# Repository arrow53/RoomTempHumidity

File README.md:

# RoomTempHumidity

A local whole-house temperature and humidity monitor. USB-powered room sensors
send measurements over Thread to a Raspberry Pi base unit, which stores history
and presents a touchscreen dashboard without requiring a cloud service.

## Actual Pi dashboard

Direct capture of the running Pi display on **2026-10-11**. This is the live-mode
application with one reporting prototype sensor, not simulated data. Readings and
freshness reflect the capture time.

## Design summary

```mermaid
flowchart LR
  S["USB room node<br/>SHT40 + nRF54L15"] -->|"Thread IPv6 / CoAP JSON"| R["nRF52840 DK<br/>RCP"]
  R -->|"Spinel / USB serial<br/>115200 RTS/CTS"| O["Pi 5<br/>OpenThread Border Router"]
  O --> C["Python collector<br/>aiocoap + SQLite"]
  C -->|"Loopback HTTP"| D["Browser kiosk<br/>Touch Display 2"]
```

- **Sensors:** SHT40 measures temperature and relative humidity. nRF54L15 firmware
  uses Zephyr and OpenThread, samples every minute and sends confirmable CoAP POSTs.
  Random boot IDs and sequence numbers support duplicate/replay handling. Continuous
  USB power permits an always-listening Thread router role.
- **Base radio:** pinned OpenThread RCP firmware on an nRF52840 DK connects over
  Spinel/UART through USB serial. It is separate from the sensor-node application.
- **Networking:** OTBR runs on the Pi 5. Recorded deployment limits forwarding to
  the intended local IPv6 LAN; IPv4 forwarding, NAT64, WebGUI and REST are disabled.
- **Collector/UI:** Python validates readings and stores bounded SQLite history.
  HTML/CSS/JavaScript provides room status, history and Celsius/Fahrenheit controls.
  CoAP bind retries keep the local dashboard available while a Thread address is
  missing. The Touch Display 2 presents the landscape browser/kiosk UI.
- **Protocol:** Thread + IPv6 + CoAP.

## Sensor hardware

| Enclosure A2 | Populated PCB A3 — angled 3D view |
| --- | --- |
|  |  |

The enclosure is a native OpenSCAD render. The populated PCB is a native KiCad
3D render of the unchanged A3 layout and its 16 component placements. Package
models show nominal geometry; the radio module uses a simplified dimension-based
body/shield. Neither image proves assembled hardware qualification.

The working prototype uses an **nRF54L15 DK and SHT40 breakout**. The custom
45 × 55 mm PCB uses Raytac AN54LQ-P15 and SHT40; A3 changes the regulator to
LT1761IS5-3.3#TRMPBF. Custom-board bring-up, printed fit, RF performance and thermal
bias remain unqualified. A3 is **quote/DFM only**, not production/purchase approval.

## Repository layout

| Directory | Contents |
| --- | --- |
| [SensorFirmware](SensorFirmware/README.md) | nRF54L15 DK firmware, pinned SDK manifest, schema and tests |
| [SensorCase](SensorCase/README.md) | A2 OpenSCAD, provisional print parts and fit coupons |
| [SensorPCB](SensorPCB/README.md) | Current A3 native KiCad and selected quote/DFM files |
| [BaseUnitFirmware](BaseUnitFirmware/README.md) | Pinned nRF52840 RCP source/build/UART reference |
| [BaseUnitApplication](BaseUnitApplication/README.md) | Pi collector/dashboard and sanitized OTBR reference |
| [BaseUnitCase](BaseUnitCase/README.md) | Revision C digital prototype, CAD and [print files](BaseUnitCase/revision-C/); physical validation pending |

Canonical workspace: `C:\GIT\RoomTempHumidity`. Future tasks should read
[AGENTS.md](AGENTS.md) and [migration notes](docs/MIGRATION.md).

## Technologies and methodology

Sensor firmware uses C, Nordic nRF Connect SDK **v3.2.1**, Zephyr and OpenThread.
RCP and OTBR use separate immutable upstream commits. OTBR's documented historical
build uses Debug after optimized builds failed a compiler diagnostic; warning and
runtime compatibility checks were retained.

The Pi application uses Python 3.11+, aiocoap, SQLite and HTML/CSS/JavaScript.
Mechanical design uses parametric OpenSCAD (sensor) and CadQuery (base case), static dimension checks and independent
STL topology checks. PCB work uses native KiCad schematic/layout, project-local
libraries, ERC/DRC and independent manufacturing-file audits.

Source, protocol fixtures and validation limits are preserved separately from local
deployment configuration. Historical hardware success is distinguished from checks
rerun on this migrated snapshot:

| Check | Publication preparation |
| --- | --- |
| Dashboard/collector | **26 tests passed**, including loopback IPv6 CoAP, replay/storage and startup recovery |
| Sensor firmware schema | **12 tests passed** |
| Enclosure static checks | **59 passed** |
| Five primary STL meshes | **5 passed** topology/dimension checks |
| Full target/RCP/OTBR builds | Historical success documented; not rebuilt here |
| Custom PCB / printed-case qualification | Pending |

## Getting started and limits

Use the [application preview](BaseUnitApplication/README.md),
[sensor build reference](SensorFirmware/README.md),
[RCP reference](BaseUnitFirmware/README.md) and [OTBR notes](BaseUnitApplication/OTBR.md).
Install tools outside the repository. Real room mappings, collector addresses and
commissioning credentials belong in local ignored configuration.

This is an engineering source snapshot, **not a turnkey OS image or production
release**. Site-specific OTBR service/firewall/rollback files, full historical
quotation archives and vendor 3D model bundles are omitted. See
[dependency limits](docs/MIGRATION.md), [image provenance](docs/images/README.md)
and [licensing notice](LICENSE-NOTICE.md). The base-unit enclosure Revision C digital design is complete; insert, cable,
slicer and physical checks remain outstanding. See its [assembly and print checklist](BaseUnitCase/revision-C/CONFIRMED-HARDWARE-FIT.txt).

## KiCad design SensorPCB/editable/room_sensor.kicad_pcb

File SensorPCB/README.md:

# Sensor PCB A3

Current manufacturing revision: **A3-Q10-quote-v1**. These are quote/DFM review
files, not a production release, purchase approval or validated assembled prototype.

Open `editable/room_sensor.kicad_pro`. Its project-local symbols and footprints
travel with the project. `fabrication/` contains selected Gerbers/drills;
`assembly/` contains the ten-board BOM, placements and DNP/board-feature table.
The native CAD and selected manufacturing files were copied unchanged and hash-checked.
Do not regenerate A3 using older A2 construction scripts.

A3 changes the regulator to LT1761IS5-3.3#TRMPBF and its local layout. The 45 x 55 mm
board outline, mounting positions and enclosure interface remain unchanged. Native
ERC/DRC and manufacturing audits passed in the original engineering work; this
publication did not rerun KiCad or qualify physical hardware.

Full original quote ZIPs, third-party datasheets, official vendor 3D models, assembled
STEP exports, historical A2 sources and raw review logs remain outside this snapshot.
No rendered 3D model completeness is implied. Refer to the original full reviewed
quote package before fabrication; USB process/tolerance and programming/test scope
remain open. Additional source/assembly/DFM documents will be included only after
their privacy, completeness and redistribution review.

Project-specific geometry was generated locally. Manufacturer names and part numbers
identify intended components, not supplier certification. Upstream KiCad library or
vendor assets added later retain their own licenses and attribution requirements.

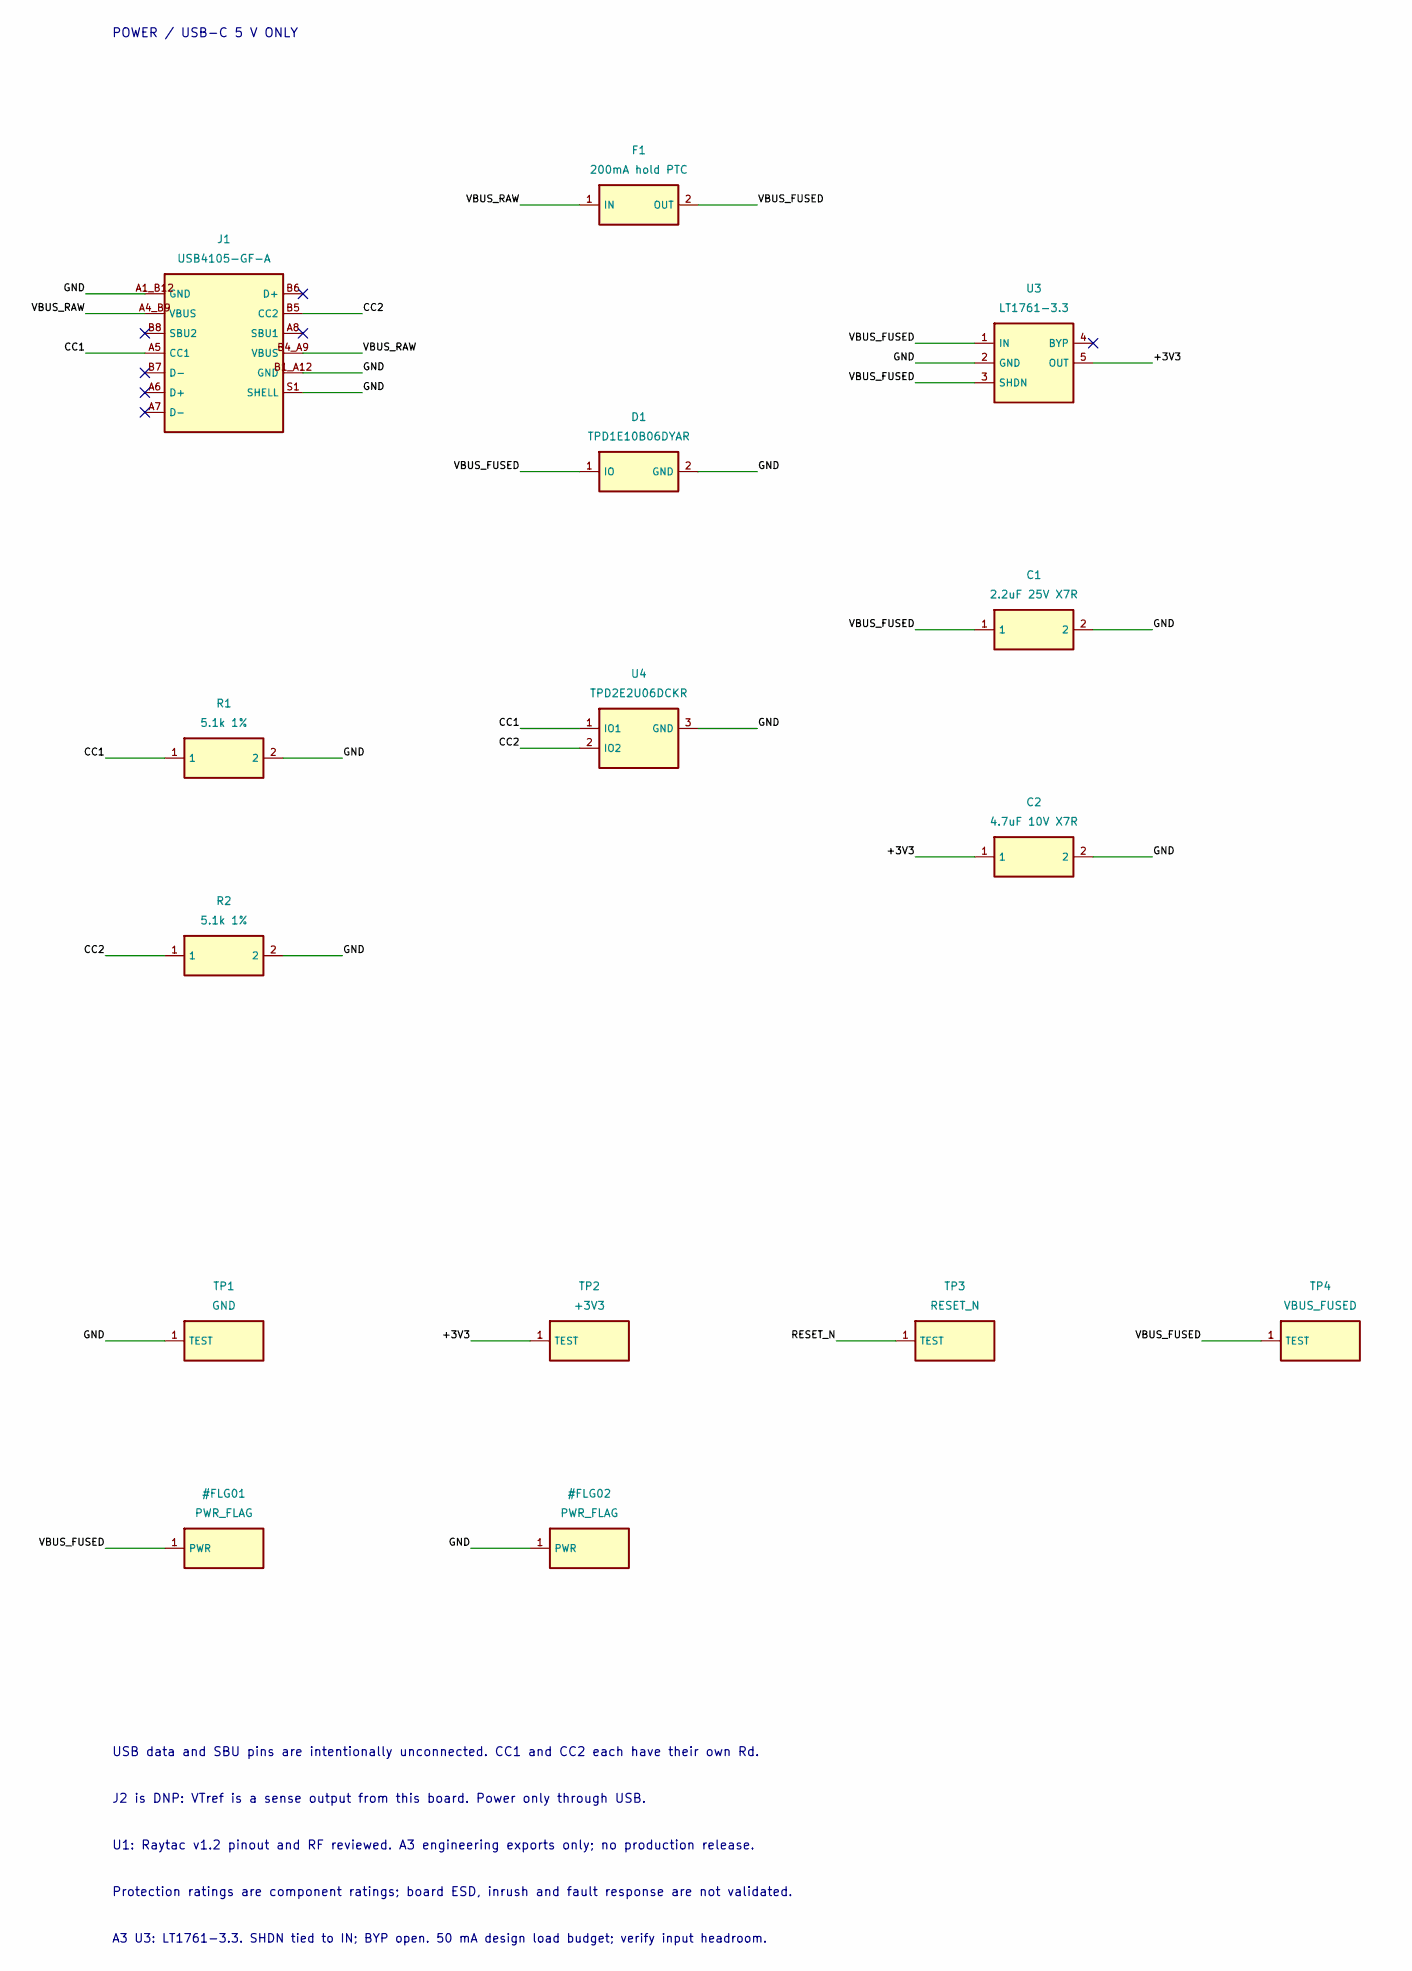
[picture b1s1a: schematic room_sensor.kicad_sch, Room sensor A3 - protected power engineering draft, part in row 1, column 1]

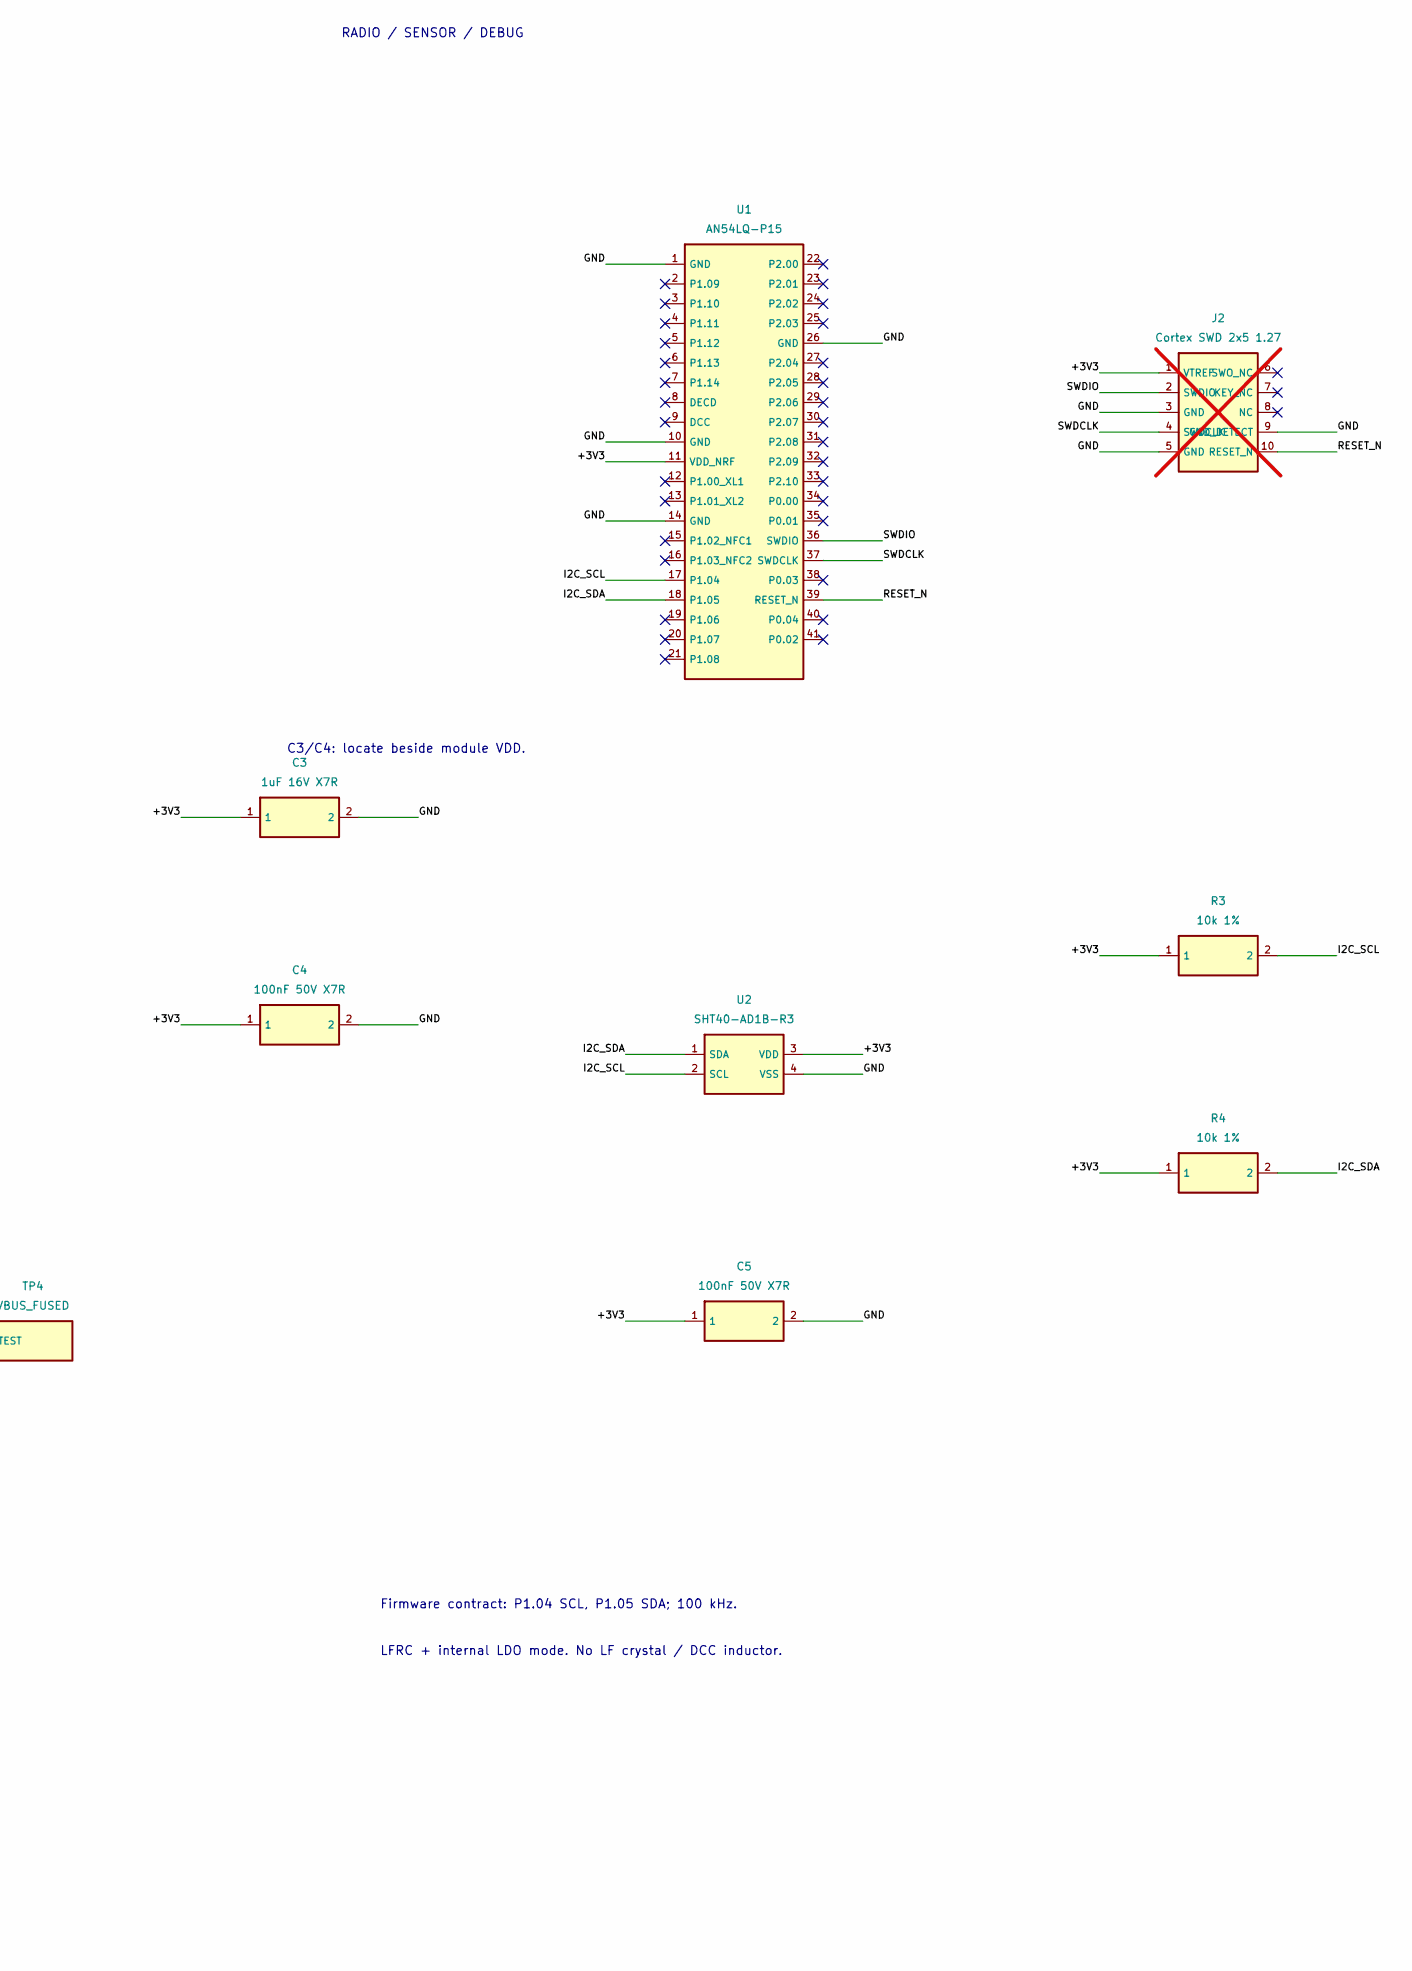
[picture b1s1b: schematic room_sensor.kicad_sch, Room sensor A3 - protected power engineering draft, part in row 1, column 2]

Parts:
C1: 2.2uF 25V X7R; C_0805; MPN C2012X7R1E225K125AB
C2: 4.7uF 10V X7R; C_0805; MPN C2012X7R1A475K125AC
C3: 1uF 16V X7R; C_0603; MPN C1608X7R1C105K080AC
C4, C5: 100nF 50V X7R; C_0603; MPN C1608X7R1H104K080AA
D1: TPD1E10B06DYAR; SOD523; MPN TPD1E10B06DYAR
F1: 200mA hold PTC; PTC_1812; MPN MF-MSMF020-2
J1: USB4105-GF-A; USB4105_Custom; MPN USB4105-GF-A
J2: Cortex SWD 2x5 1.27; SWD_2x5_1p27; MPN DNP: pogo or header selected later; not fitted
R1, R2: 5.1k 1%; R_0603; MPN RC0603FR-075K1L
R3, R4: 10k 1%; R_0603; MPN RC0603FR-0710KL
TP1: GND; TestPoint_1mm; MPN PCB copper feature
TP2: +3V3; TestPoint_1mm; MPN PCB copper feature
TP3: RESET_N; TestPoint_1mm; MPN PCB copper feature
TP4: VBUS_FUSED; TestPoint_1mm; MPN PCB copper feature
U1: AN54LQ-P15; AN54LQ_P15_DRAFT; MPN MD-240A8-002
U2: SHT40-AD1B-R3; SHT40_DFN4; MPN SHT40-AD1B-R3
U3: LT1761-3.3; LT1761_TSOT23_5; MPN LT1761IS5-3.3#TRMPBF
U4: TPD2E2U06DCKR; SC70_3; MPN TPD2E2U06DCKR

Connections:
/+3V3: C2.1, C3.1, C4.1, C5.1, J2.1 (VTREF), R3.1, R4.1, TP2.1, U1.11 (VDD_NRF), U2.3 (VDD), U3.5 (OUT)
/CC1: J1.A5 (CC1), R1.1, U4.1 (IO1)
/CC2: J1.B5 (CC2), R2.1, U4.2 (IO2)
/GND: C1.2, C2.2, C3.2, C4.2, C5.2, D1.2 (GND), J1.A1_B12 (GND), J1.B1_A12 (GND), J1.S1 (SHELL), J2.3 (GND), J2.5 (GND), J2.9 (GND_DETECT), R1.2, R2.2, TP1.1, U1.1 (GND), U1.10 (GND), U1.14 (GND), U1.26 (GND), U2.4 (VSS), U3.2 (GND), U4.3 (GND)
/I2C_SCL: R3.2, U1.17 (P1.04), U2.2 (SCL)
/I2C_SDA: R4.2, U1.18 (P1.05), U2.1 (SDA)
/RESET_N: J2.10 (RESET_N), TP3.1, U1.39 (RESET_N)
/SWDCLK: J2.4 (SWDCLK), U1.37 (SWDCLK)
/SWDIO: J2.2 (SWDIO), U1.36 (SWDIO)
/VBUS_FUSED: C1.1, D1.1 (IO), F1.2 (OUT), TP4.1, U3.1 (IN), U3.3 (SHDN)
/VBUS_RAW: F1.1 (IN), J1.A4_B9 (VBUS), J1.B4_A9 (VBUS)

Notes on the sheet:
POWER / USB-C 5 V ONLY
RADIO / SENSOR / DEBUG
C3/C4: locate beside module VDD.
Firmware contract: P1.04 SCL, P1.05 SDA; 100 kHz.
LFRC + internal LDO mode. No LF crystal / DCC inductor.
USB data and SBU pins are intentionally unconnected. CC1 and CC2 each have their own Rd.
J2 is DNP: VTref is a sense output from this board. Power only through USB.
U1: Raytac v1.2 pinout and RF reviewed. A3 engineering exports only; no production release.
Protection ratings are component ratings; board ESD, inrush and fault response are not validated.
A3 U3: LT1761-3.3. SHDN tied to IN; BYP open. 50 mA design load budget; verify input headroom.

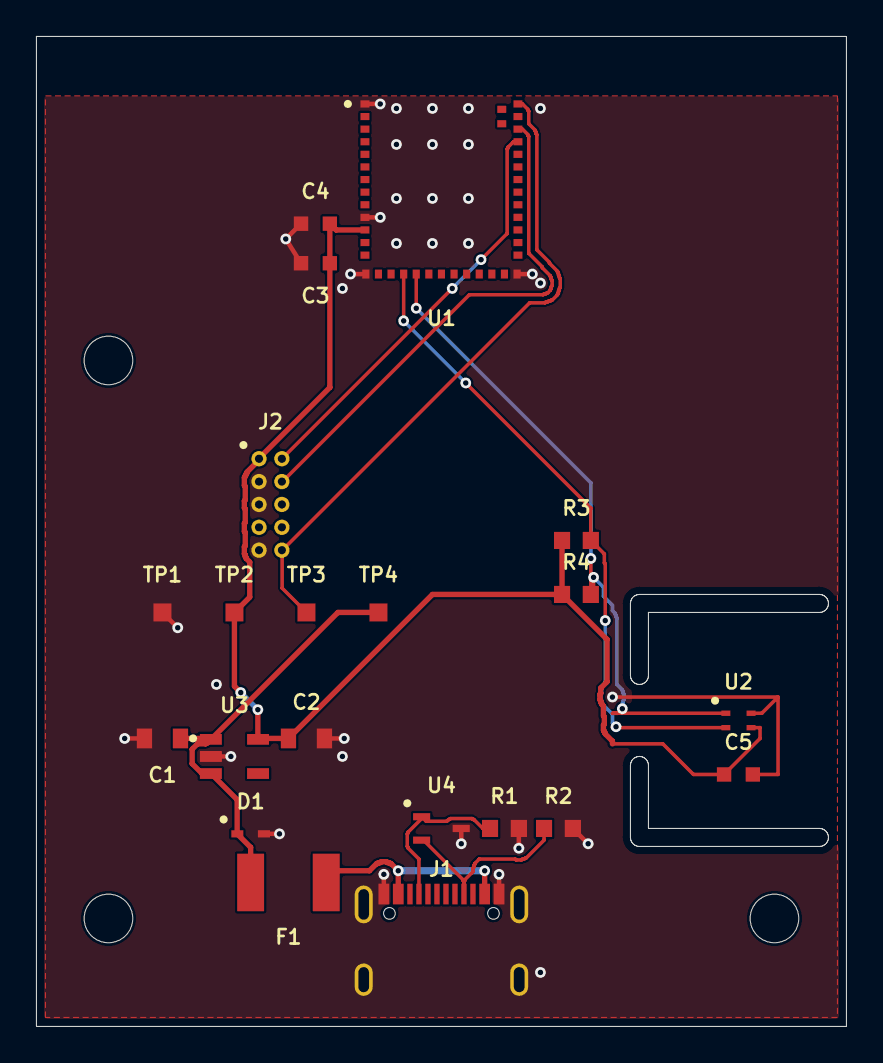
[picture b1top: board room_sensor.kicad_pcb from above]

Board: 2 copper layers, 45.0 x 55.0 mm, 24 parts (0 on the bottom side), 11 nets.

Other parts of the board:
H1, H2, H3: MountingHole_2.7
